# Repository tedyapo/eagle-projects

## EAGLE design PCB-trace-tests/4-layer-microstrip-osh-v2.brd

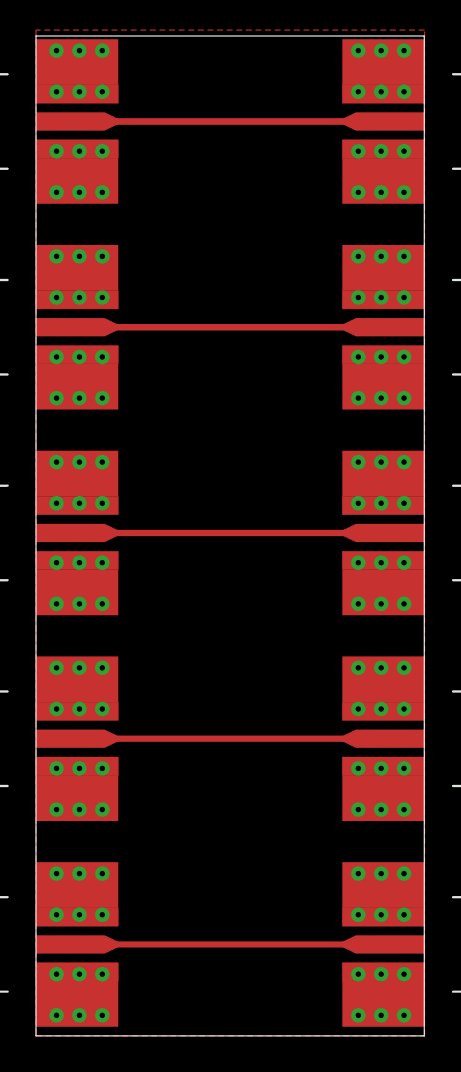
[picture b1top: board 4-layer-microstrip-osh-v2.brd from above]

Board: 2 copper layers, 21.6 x 55.5 mm, 10 parts (0 on the bottom side), 6 nets.

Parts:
J1, J2, J3, J4, J5, J6, J7, J8, J9, J10: SMA_EDGE_LAUNCH_4L_4020_TAPER_FIXED

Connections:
GND: J1.BOTTOM_GND, J1.GND@1, J1.GND@2, J1.GND@3, J1.GND@4, J1.GND@5, J1.GND@6, J1.GND@7, J1.GND@8, J1.GND@14, J1.GND@15, J1.GND@16, J1.GND@17, J1.GND_PAD1, J1.GND_PAD2, J1.P$1, J1.P$2, J2.BOTTOM_GND, J2.GND@1, J2.GND@2, J2.GND@3, J2.GND@4, J2.GND@5, J2.GND@6, J2.GND@7, J2.GND@8, J2.GND@14, J2.GND@15, J2.GND@16, J2.GND@17, J2.GND_PAD1, J2.GND_PAD2, J2.P$1, J2.P$2, J3.BOTTOM_GND, J3.GND@1, J3.GND@2, J3.GND@3, J3.GND@4, J3.GND@5, J3.GND@6, J3.GND@7, J3.GND@8, J3.GND@14, J3.GND@15, J3.GND@16, J3.GND@17, J3.GND_PAD1, J3.GND_PAD2, J3.P$1, J3.P$2, J4.BOTTOM_GND, J4.GND@1, J4.GND@2, J4.GND@3, J4.GND@4, J4.GND@5, J4.GND@6, J4.GND@7, J4.GND@8, J4.GND@14, J4.GND@15, J4.GND@16, J4.GND@17, J4.GND_PAD1, J4.GND_PAD2, J4.P$1, J4.P$2, J5.BOTTOM_GND, J5.GND@1, J5.GND@2, J5.GND@3, J5.GND@4, J5.GND@5, J5.GND@6, J5.GND@7, J5.GND@8, J5.GND@14, J5.GND@15, J5.GND@16, J5.GND@17, J5.GND_PAD1, J5.GND_PAD2, J5.P$1, J5.P$2, J6.BOTTOM_GND, J6.GND@1, J6.GND@2, J6.GND@3, J6.GND@4, J6.GND@5, J6.GND@6, J6.GND@7, J6.GND@8, J6.GND@14, J6.GND@15, J6.GND@16, J6.GND@17, J6.GND_PAD1, J6.GND_PAD2, J6.P$1, J6.P$2, J7.BOTTOM_GND, J7.GND@1, J7.GND@2, J7.GND@3, J7.GND@4, J7.GND@5, J7.GND@6, J7.GND@7, J7.GND@8, J7.GND@14, J7.GND@15, J7.GND@16, J7.GND@17, J7.GND_PAD1, J7.GND_PAD2, J7.P$1, J7.P$2, J8.BOTTOM_GND, J8.GND@1, J8.GND@2, J8.GND@3, J8.GND@4, J8.GND@5, J8.GND@6, J8.GND@7, J8.GND@8, J8.GND@14, J8.GND@15, J8.GND@16, J8.GND@17, J8.GND_PAD1, J8.GND_PAD2, J8.P$1, J8.P$2, J9.BOTTOM_GND, J9.GND@1, J9.GND@2, J9.GND@3, J9.GND@4, J9.GND@5, J9.GND@6, J9.GND@7, J9.GND@8, J9.GND@14, J9.GND@15, J9.GND@16, J9.GND@17, J9.GND_PAD1, J9.GND_PAD2, J9.P$1, J9.P$2, J10.BOTTOM_GND, J10.GND@1, J10.GND@2, J10.GND@3, J10.GND@4, J10.GND@5, J10.GND@6, J10.GND@7, J10.GND@8, J10.GND@14, J10.GND@15, J10.GND@16, J10.GND@17, J10.GND_PAD1, J10.GND_PAD2, J10.P$1, J10.P$2
unnamed: J1.CENTER@1, J1.P$3, J2.CENTER@1, J2.P$3
unnamed: J3.CENTER@1, J3.P$3, J4.CENTER@1, J4.P$3
unnamed: J5.CENTER@1, J5.P$3, J6.CENTER@1, J6.P$3
unnamed: J7.CENTER@1, J7.P$3, J8.CENTER@1, J8.P$3
unnamed: J9.CENTER@1, J9.P$3, J10.CENTER@1, J10.P$3

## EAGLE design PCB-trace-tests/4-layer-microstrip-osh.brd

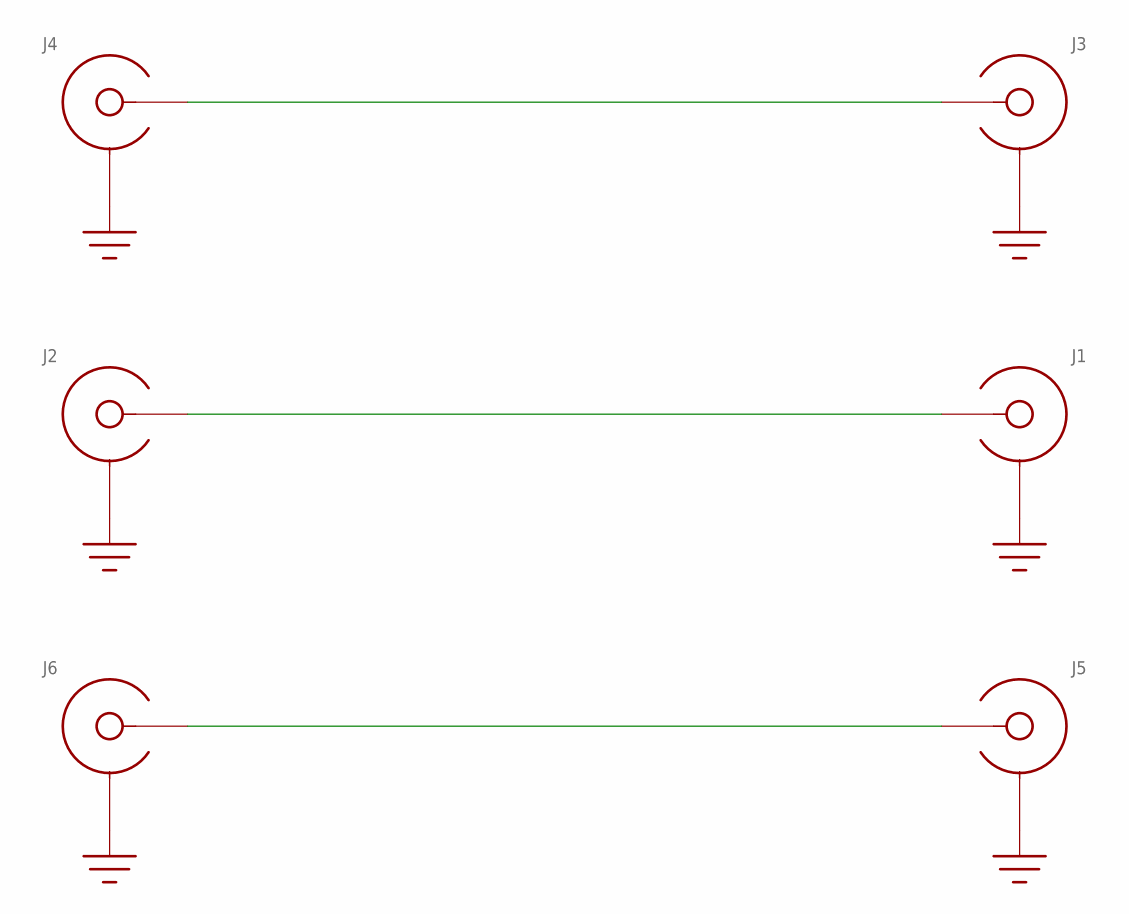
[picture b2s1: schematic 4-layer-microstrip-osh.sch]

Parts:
J1: SMA-EDGE-LAUNCH4L_4045_TAPER; SMA_EDGE_LAUNCH_4L_4045_TAPER
J2: SMA-EDGE-LAUNCH4L_4040_TAPER; SMA_EDGE_LAUNCH_4L_4040_TAPER
J3: SMA-EDGE-LAUNCH4L_4035_TAPER; SMA_EDGE_LAUNCH_4L_4035_TAPER
J4: SMA-EDGE-LAUNCH4L_4020_TAPER; SMA_EDGE_LAUNCH_4L_4020_TAPER
J5: SMA-EDGE-LAUNCH4L_4030_TAPER; SMA_EDGE_LAUNCH_4L_4030_TAPER
J6: SMA-EDGE-LAUNCH4L_4025_TAPER; SMA_EDGE_LAUNCH_4L_4025_TAPER

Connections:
GND: J1.BOTTOM_GND (SHIELD), J1.GND@1 (SHIELD), J1.GND@2 (SHIELD), J1.GND@3 (SHIELD), J1.GND@4 (SHIELD), J1.GND@5 (SHIELD), J1.GND@6 (SHIELD), J1.GND@7 (SHIELD), J1.GND@8 (SHIELD), J1.GND@14 (SHIELD), J1.GND@15 (SHIELD), J1.GND@16 (SHIELD), J1.GND@17 (SHIELD), J1.GND_PAD1 (SHIELD), J1.GND_PAD2 (SHIELD), J1.P$1 (SHIELD), J1.P$2 (SHIELD), J2.BOTTOM_GND (SHIELD), J2.GND@1 (SHIELD), J2.GND@2 (SHIELD), J2.GND@3 (SHIELD), J2.GND@4 (SHIELD), J2.GND@5 (SHIELD), J2.GND@6 (SHIELD), J2.GND@7 (SHIELD), J2.GND@8 (SHIELD), J2.GND@14 (SHIELD), J2.GND@15 (SHIELD), J2.GND@16 (SHIELD), J2.GND@17 (SHIELD), J2.GND_PAD1 (SHIELD), J2.GND_PAD2 (SHIELD), J2.P$1 (SHIELD), J2.P$2 (SHIELD), J3.BOTTOM_GND (SHIELD), J3.GND@1 (SHIELD), J3.GND@2 (SHIELD), J3.GND@3 (SHIELD), J3.GND@4 (SHIELD), J3.GND@5 (SHIELD), J3.GND@6 (SHIELD), J3.GND@7 (SHIELD), J3.GND@8 (SHIELD), J3.GND@14 (SHIELD), J3.GND@15 (SHIELD), J3.GND@16 (SHIELD), J3.GND@17 (SHIELD), J3.GND_PAD1 (SHIELD), J3.GND_PAD2 (SHIELD), J3.P$1 (SHIELD), J3.P$2 (SHIELD), J4.BOTTOM_GND (SHIELD), J4.GND@1 (SHIELD), J4.GND@2 (SHIELD), J4.GND@3 (SHIELD), J4.GND@4 (SHIELD), J4.GND@5 (SHIELD), J4.GND@6 (SHIELD), J4.GND@7 (SHIELD), J4.GND@8 (SHIELD), J4.GND@14 (SHIELD), J4.GND@15 (SHIELD), J4.GND@16 (SHIELD), J4.GND@17 (SHIELD), J4.GND_PAD1 (SHIELD), J4.GND_PAD2 (SHIELD), J4.P$1 (SHIELD), J4.P$2 (SHIELD), J5.BOTTOM_GND (SHIELD), J5.GND@1 (SHIELD), J5.GND@2 (SHIELD), J5.GND@3 (SHIELD), J5.GND@4 (SHIELD), J5.GND@5 (SHIELD), J5.GND@6 (SHIELD), J5.GND@7 (SHIELD), J5.GND@8 (SHIELD), J5.GND@14 (SHIELD), J5.GND@15 (SHIELD), J5.GND@16 (SHIELD), J5.GND@17 (SHIELD), J5.GND_PAD1 (SHIELD), J5.GND_PAD2 (SHIELD), J5.P$1 (SHIELD), J5.P$2 (SHIELD), J6.BOTTOM_GND (SHIELD), J6.GND@1 (SHIELD), J6.GND@2 (SHIELD), J6.GND@3 (SHIELD), J6.GND@4 (SHIELD), J6.GND@5 (SHIELD), J6.GND@6 (SHIELD), J6.GND@7 (SHIELD), J6.GND@8 (SHIELD), J6.GND@14 (SHIELD), J6.GND@15 (SHIELD), J6.GND@16 (SHIELD), J6.GND@17 (SHIELD), J6.GND_PAD1 (SHIELD), J6.GND_PAD2 (SHIELD), J6.P$1 (SHIELD), J6.P$2 (SHIELD)
unnamed: J1.CENTER@1 (CENTER), J2.CENTER@1 (CENTER)
unnamed: J3.CENTER@1 (CENTER), J4.CENTER@1 (CENTER)
unnamed: J5.CENTER@1 (CENTER), J6.CENTER@1 (CENTER)

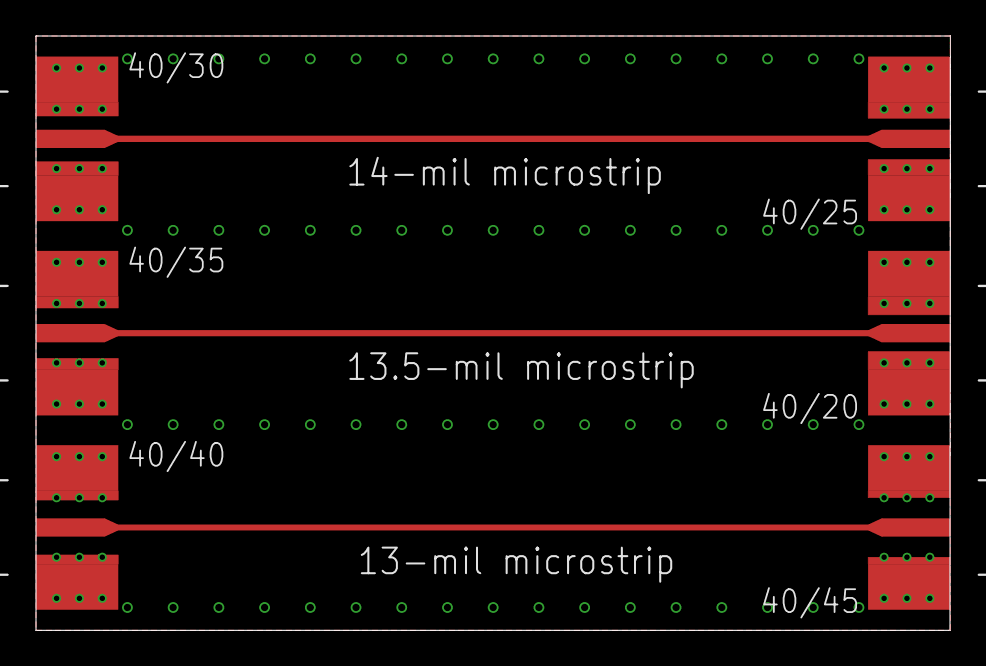
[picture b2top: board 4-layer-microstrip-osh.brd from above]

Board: 4 copper layers, 50.8 x 33.0 mm, 6 parts (0 on the bottom side), 4 nets.

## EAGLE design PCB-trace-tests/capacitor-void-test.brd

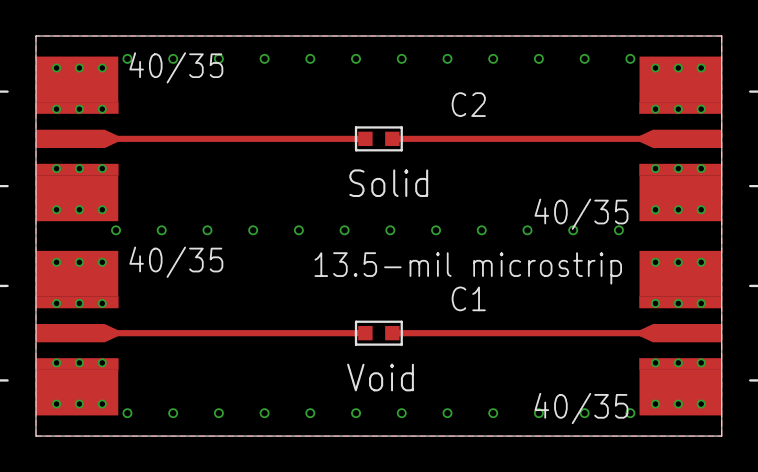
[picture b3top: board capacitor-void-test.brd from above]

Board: 4 copper layers, 38.1 x 22.2 mm, 6 parts (0 on the bottom side), 5 nets.

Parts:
C1: C0603_VOID
C2: C0603
J1, J2, J3, J4: SMA_EDGE_LAUNCH_4L_4035_TAPER

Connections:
GND: J1.BOTTOM_GND, J1.GND@1, J1.GND@2, J1.GND@3, J1.GND@4, J1.GND@5, J1.GND@6, J1.GND@7, J1.GND@8, J1.GND@14, J1.GND@15, J1.GND@16, J1.GND@17, J1.GND_PAD1, J1.GND_PAD2, J1.P$1, J1.P$2, J2.BOTTOM_GND, J2.GND@1, J2.GND@2, J2.GND@3, J2.GND@4, J2.GND@5, J2.GND@6, J2.GND@7, J2.GND@8, J2.GND@14, J2.GND@15, J2.GND@16, J2.GND@17, J2.GND_PAD1, J2.GND_PAD2, J2.P$1, J2.P$2, J3.BOTTOM_GND, J3.GND@1, J3.GND@2, J3.GND@3, J3.GND@4, J3.GND@5, J3.GND@6, J3.GND@7, J3.GND@8, J3.GND@14, J3.GND@15, J3.GND@16, J3.GND@17, J3.GND_PAD1, J3.GND_PAD2, J3.P$1, J3.P$2, J4.BOTTOM_GND, J4.GND@1, J4.GND@2, J4.GND@3, J4.GND@4, J4.GND@5, J4.GND@6, J4.GND@7, J4.GND@8, J4.GND@14, J4.GND@15, J4.GND@16, J4.GND@17, J4.GND_PAD1, J4.GND_PAD2, J4.P$1, J4.P$2
unnamed: C1.P$2, J2.CENTER@1
unnamed: C1.P$1, J1.CENTER@1
unnamed: C2.P$2, J4.CENTER@1
unnamed: C2.P$1, J3.CENTER@1

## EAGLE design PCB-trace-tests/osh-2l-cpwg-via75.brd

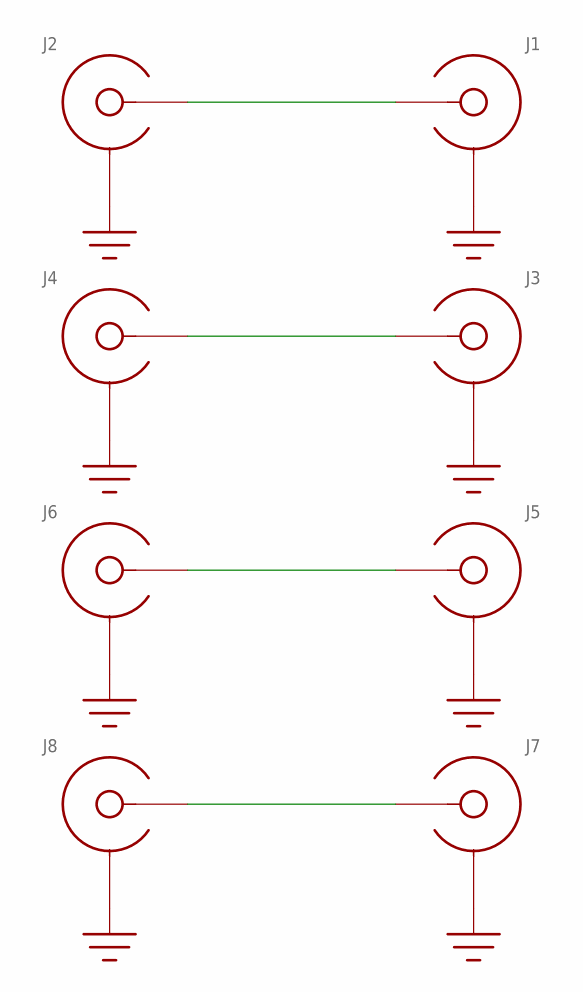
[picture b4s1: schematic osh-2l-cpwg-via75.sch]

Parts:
J1, J3, J5, J7: SMA-EDGE-LAUNCH4020_TAPER; SMA_EDGE_LAUNCH_2L_4020_TAPER
J2, J4, J6, J8: SMA-EDGE-LAUNCHCUT-PIN; SMA_EDGE_LAUNCH_2L_4020_CUT_PIN

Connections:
GND: J1.BOTTOM_GND (SHIELD), J1.GND@1 (SHIELD), J1.GND@2 (SHIELD), J1.GND@3 (SHIELD), J1.GND@4 (SHIELD), J1.GND@5 (SHIELD), J1.GND@6 (SHIELD), J1.GND@7 (SHIELD), J1.GND@8 (SHIELD), J1.GND@14 (SHIELD), J1.GND@15 (SHIELD), J1.GND@16 (SHIELD), J1.GND@17 (SHIELD), J1.GND_PAD1 (SHIELD), J1.GND_PAD2 (SHIELD), J1.P$1 (SHIELD), J1.P$2 (SHIELD), J2.BOTTOM_GND (SHIELD), J2.GND@1 (SHIELD), J2.GND@2 (SHIELD), J2.GND@3 (SHIELD), J2.GND@4 (SHIELD), J2.GND@5 (SHIELD), J2.GND@6 (SHIELD), J2.GND@7 (SHIELD), J2.GND@8 (SHIELD), J2.GND@14 (SHIELD), J2.GND@15 (SHIELD), J2.GND@16 (SHIELD), J2.GND@17 (SHIELD), J2.GND_PAD1 (SHIELD), J2.GND_PAD2 (SHIELD), J3.BOTTOM_GND (SHIELD), J3.GND@1 (SHIELD), J3.GND@2 (SHIELD), J3.GND@3 (SHIELD), J3.GND@4 (SHIELD), J3.GND@5 (SHIELD), J3.GND@6 (SHIELD), J3.GND@7 (SHIELD), J3.GND@8 (SHIELD), J3.GND@14 (SHIELD), J3.GND@15 (SHIELD), J3.GND@16 (SHIELD), J3.GND@17 (SHIELD), J3.GND_PAD1 (SHIELD), J3.GND_PAD2 (SHIELD), J3.P$1 (SHIELD), J3.P$2 (SHIELD), J4.BOTTOM_GND (SHIELD), J4.GND@1 (SHIELD), J4.GND@2 (SHIELD), J4.GND@3 (SHIELD), J4.GND@4 (SHIELD), J4.GND@5 (SHIELD), J4.GND@6 (SHIELD), J4.GND@7 (SHIELD), J4.GND@8 (SHIELD), J4.GND@14 (SHIELD), J4.GND@15 (SHIELD), J4.GND@16 (SHIELD), J4.GND@17 (SHIELD), J4.GND_PAD1 (SHIELD), J4.GND_PAD2 (SHIELD), J5.BOTTOM_GND (SHIELD), J5.GND@1 (SHIELD), J5.GND@2 (SHIELD), J5.GND@3 (SHIELD), J5.GND@4 (SHIELD), J5.GND@5 (SHIELD), J5.GND@6 (SHIELD), J5.GND@7 (SHIELD), J5.GND@8 (SHIELD), J5.GND@14 (SHIELD), J5.GND@15 (SHIELD), J5.GND@16 (SHIELD), J5.GND@17 (SHIELD), J5.GND_PAD1 (SHIELD), J5.GND_PAD2 (SHIELD), J5.P$1 (SHIELD), J5.P$2 (SHIELD), J6.BOTTOM_GND (SHIELD), J6.GND@1 (SHIELD), J6.GND@2 (SHIELD), J6.GND@3 (SHIELD), J6.GND@4 (SHIELD), J6.GND@5 (SHIELD), J6.GND@6 (SHIELD), J6.GND@7 (SHIELD), J6.GND@8 (SHIELD), J6.GND@14 (SHIELD), J6.GND@15 (SHIELD), J6.GND@16 (SHIELD), J6.GND@17 (SHIELD), J6.GND_PAD1 (SHIELD), J6.GND_PAD2 (SHIELD), J7.BOTTOM_GND (SHIELD), J7.GND@1 (SHIELD), J7.GND@2 (SHIELD), J7.GND@3 (SHIELD), J7.GND@4 (SHIELD), J7.GND@5 (SHIELD), J7.GND@6 (SHIELD), J7.GND@7 (SHIELD), J7.GND@8 (SHIELD), J7.GND@14 (SHIELD), J7.GND@15 (SHIELD), J7.GND@16 (SHIELD), J7.GND@17 (SHIELD), J7.GND_PAD1 (SHIELD), J7.GND_PAD2 (SHIELD), J7.P$1 (SHIELD), J7.P$2 (SHIELD), J8.BOTTOM_GND (SHIELD), J8.GND@1 (SHIELD), J8.GND@2 (SHIELD), J8.GND@3 (SHIELD), J8.GND@4 (SHIELD), J8.GND@5 (SHIELD), J8.GND@6 (SHIELD), J8.GND@7 (SHIELD), J8.GND@8 (SHIELD), J8.GND@14 (SHIELD), J8.GND@15 (SHIELD), J8.GND@16 (SHIELD), J8.GND@17 (SHIELD), J8.GND_PAD1 (SHIELD), J8.GND_PAD2 (SHIELD)
unnamed: J1.CENTER@1 (CENTER), J2.CENTER@1 (CENTER), J2.CENTER@3 (CENTER)
unnamed: J3.CENTER@1 (CENTER), J4.CENTER@1 (CENTER), J4.CENTER@3 (CENTER)
unnamed: J5.CENTER@1 (CENTER), J6.CENTER@1 (CENTER), J6.CENTER@3 (CENTER)
unnamed: J7.CENTER@1 (CENTER), J8.CENTER@1 (CENTER), J8.CENTER@3 (CENTER)

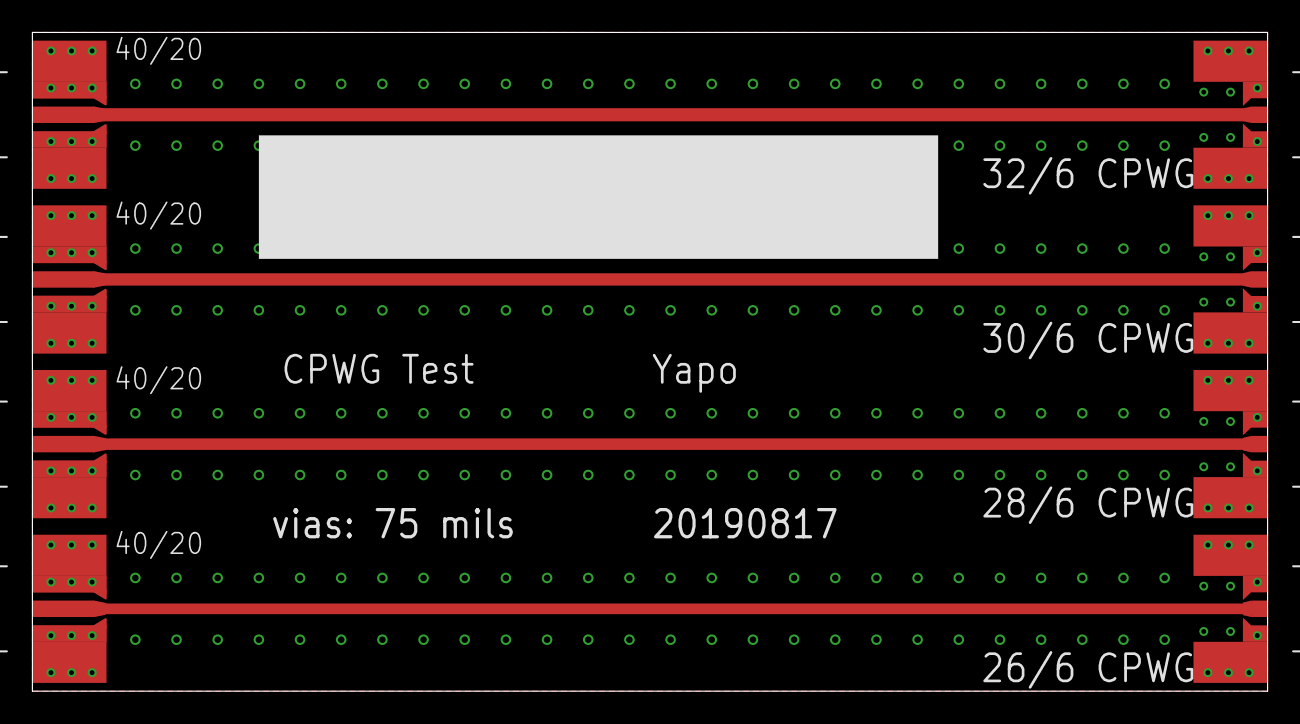
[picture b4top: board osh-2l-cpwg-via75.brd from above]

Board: 2 copper layers, 76.2 x 40.6 mm, 8 parts (0 on the bottom side), 5 nets.

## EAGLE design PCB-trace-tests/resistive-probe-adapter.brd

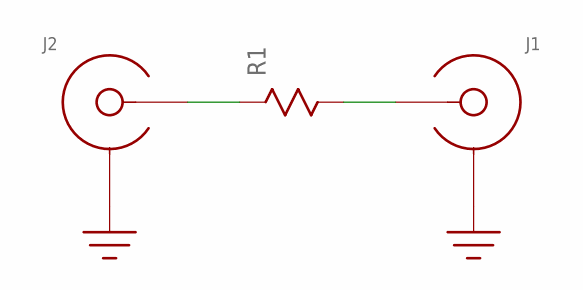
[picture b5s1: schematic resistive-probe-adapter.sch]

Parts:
J1, J2: SMA-EDGE-LAUNCH4020_TAPER; SMA_EDGE_LAUNCH_2L_4020_TAPER
R1: R0603

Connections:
GND: J1.BOTTOM_GND (SHIELD), J1.GND@1 (SHIELD), J1.GND@2 (SHIELD), J1.GND@3 (SHIELD), J1.GND@4 (SHIELD), J1.GND@5 (SHIELD), J1.GND@6 (SHIELD), J1.GND@7 (SHIELD), J1.GND@8 (SHIELD), J1.GND@14 (SHIELD), J1.GND@15 (SHIELD), J1.GND@16 (SHIELD), J1.GND@17 (SHIELD), J1.GND_PAD1 (SHIELD), J1.GND_PAD2 (SHIELD), J1.P$1 (SHIELD), J1.P$2 (SHIELD), J2.BOTTOM_GND (SHIELD), J2.GND@1 (SHIELD), J2.GND@2 (SHIELD), J2.GND@3 (SHIELD), J2.GND@4 (SHIELD), J2.GND@5 (SHIELD), J2.GND@6 (SHIELD), J2.GND@7 (SHIELD), J2.GND@8 (SHIELD), J2.GND@14 (SHIELD), J2.GND@15 (SHIELD), J2.GND@16 (SHIELD), J2.GND@17 (SHIELD), J2.GND_PAD1 (SHIELD), J2.GND_PAD2 (SHIELD), J2.P$1 (SHIELD), J2.P$2 (SHIELD)
unnamed: J2.CENTER@1 (CENTER), R1.P$1
unnamed: J1.CENTER@1 (CENTER), R1.P$2

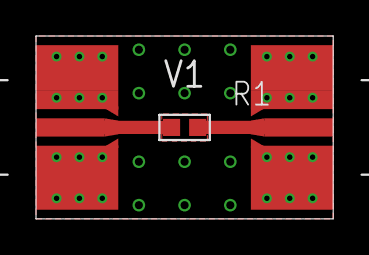
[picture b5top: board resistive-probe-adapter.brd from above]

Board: 2 copper layers, 16.5 x 10.2 mm, 3 parts (0 on the bottom side), 3 nets.
